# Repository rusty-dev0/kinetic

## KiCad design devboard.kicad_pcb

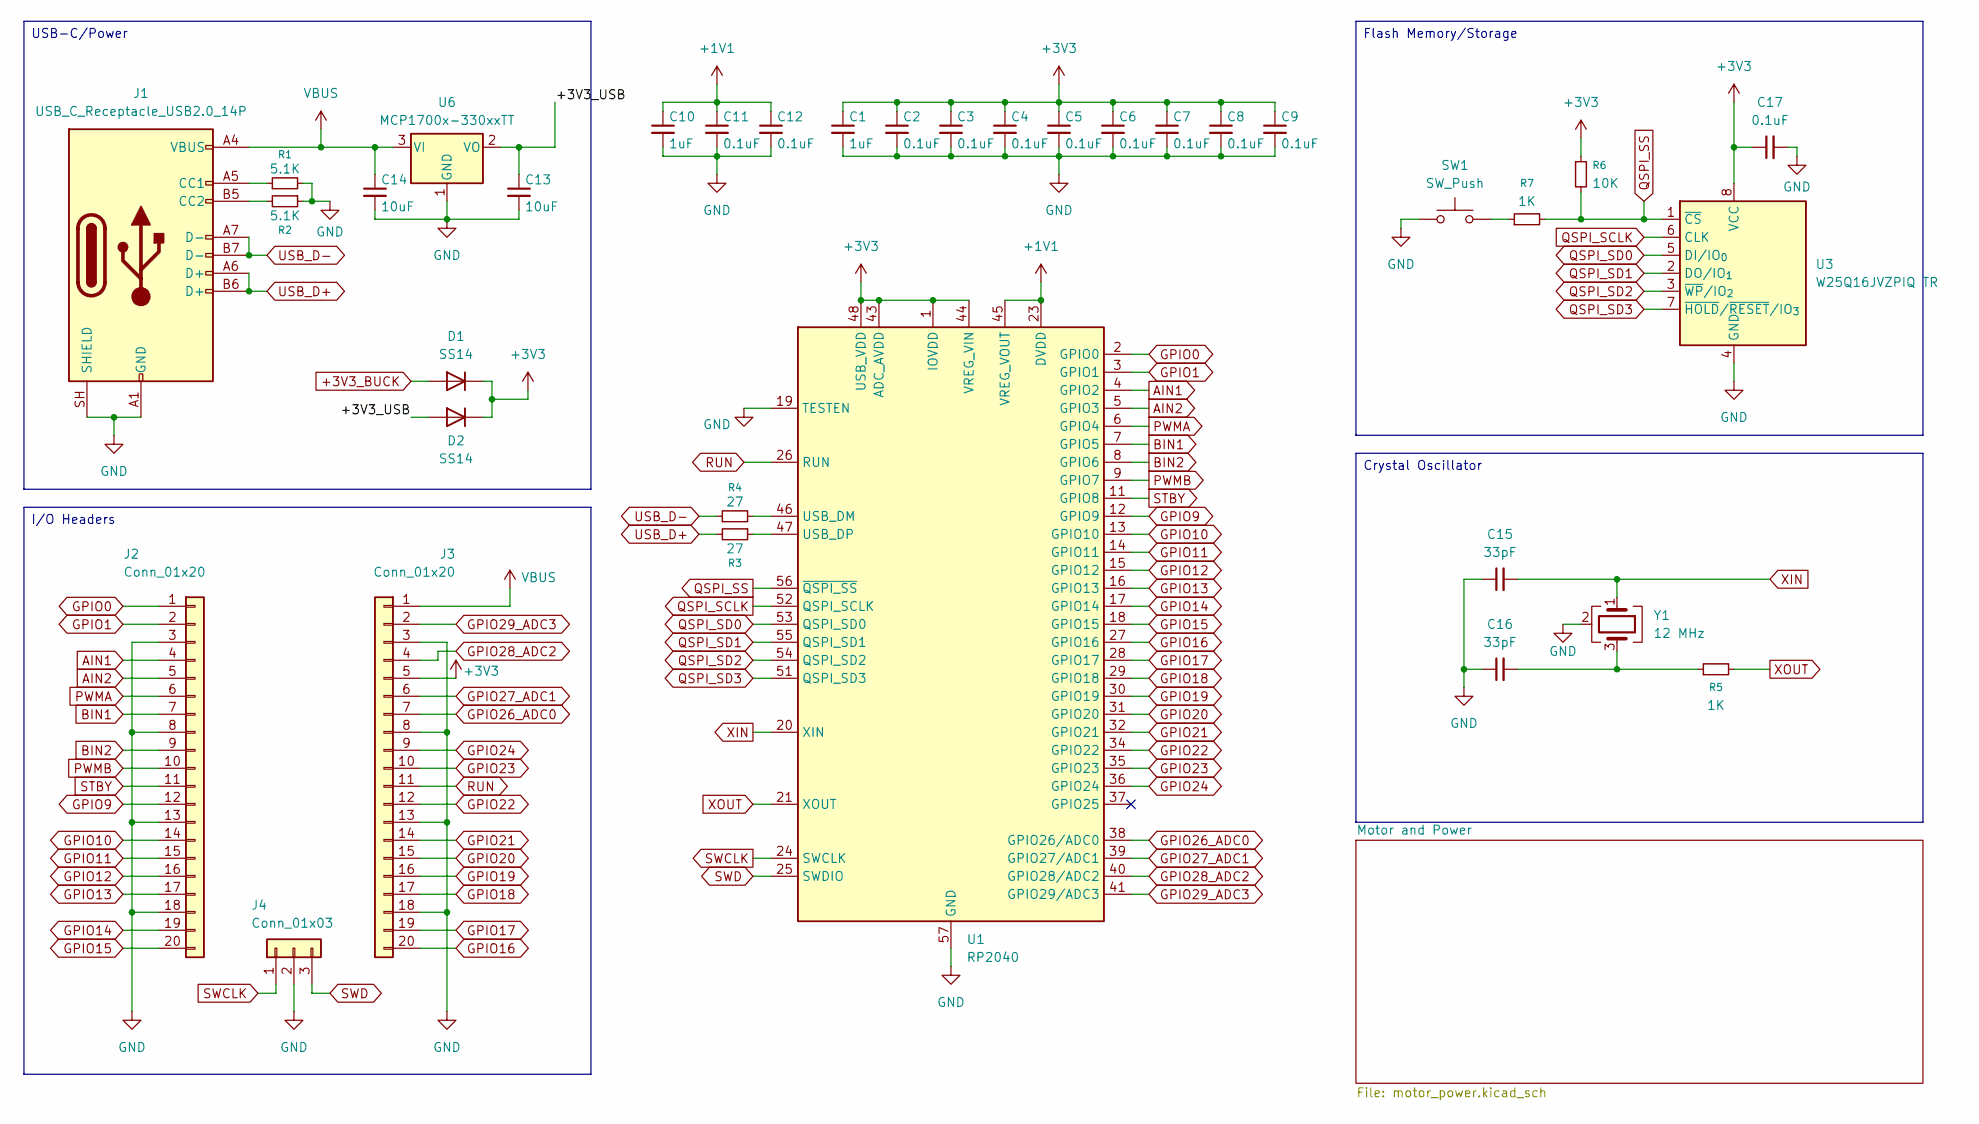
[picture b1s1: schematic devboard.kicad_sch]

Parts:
C1, C10: 1uF; C_0402_1005Metric
C2, C3, C4, C5, C6, C7, C8, C9, C11, C12, C17: 0.1uF; C_0402_1005Metric
C13, C14: 10uF; C_0603_1608Metric
C15, C16: 33pF; C_0402_1005Metric
D1, D2: SS14; D_SMA
J1: USB_C_Receptacle_USB2.0_14P; USB_C_Receptacle_HRO_TYPE-C-31-M-12
J2, J3: Conn_01x20; PinHeader_1x20_P2.54mm_Vertical
J4: Conn_01x03; FanPinHeader_1x03_P2.54mm_Vertical
R1, R2: 5.1K; R_0402_1005Metric
R3, R4: 27; R_0402_1005Metric
R5, R7: 1K; R_0402_1005Metric
R6: 10K; R_0402_1005Metric
SW1: SW_Push; SW_Push_SPST_NO_Alps_SKRK
U1: RP2040; QFN-56-1EP_7x7mm_P0.4mm_EP3.2x3.2mm
U3: W25Q16JVZPIQ TR; Winbond_USON-8-1EP_3x2mm_P0.5mm_EP0.2x1.6mm
U6: MCP1700x-330xxTT; SOT-23
Y1: 12 MHz; Crystal_SMD_3225-4Pin_3.2x2.5mm

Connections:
+1V1: C10.1, C11.1, C12.1, U1.23 (DVDD), U1.45 (VREG_VOUT), U1.50 (DVDD)
+3V3: C1.1, C2.1, C3.1, C4.1, C5.1, C6.1, C7.1, C8.1, C9.1, C17.1, D1.1 (K), D2.1 (K), J3.5, R6.1, U1.1 (IOVDD), U1.10 (IOVDD), U1.22 (IOVDD), U1.33 (IOVDD), U1.42 (IOVDD), U1.43 (ADC_AVDD), U1.44 (VREG_VIN), U1.48 (USB_VDD), U1.49 (IOVDD), U3.8 (VCC); also elsewhere on the board
+3V3_BUCK: D1.2 (A); also elsewhere on the board
/+3V3_USB: C13.1, D2.2 (A), U6.2 (VO); also elsewhere on the board
AIN1: J2.4, U1.4 (GPIO2); also elsewhere on the board
AIN2: J2.5, U1.5 (GPIO3); also elsewhere on the board
BIN1: J2.7, U1.7 (GPIO5); also elsewhere on the board
BIN2: J2.9, U1.8 (GPIO6); also elsewhere on the board
GND: C1.2, C2.2, C3.2, C4.2, C5.2, C6.2, C7.2, C8.2, C9.2, C10.2, C11.2, C12.2, C13.2, C14.2, C15.1, C16.1, C17.2, J1.A1 (GND), J1.A12 (GND), J1.B1 (GND), J1.B12 (GND), J1.SH (SHIELD), J2.3, J2.8, J2.13, J2.18, J3.3, J3.8, J3.13, J3.18, J4.2, R1.2, R2.1, SW1.1, U1.19 (TESTEN), U1.57 (GND), U3.4 (GND), U6.1 (GND), Y1.2 (G), Y1.4 (G); also elsewhere on the board
GPIO0: J2.1, U1.2 (GPIO0)
GPIO1: J2.2, U1.3 (GPIO1)
GPIO9: J2.12, U1.12 (GPIO9)
GPIO10: J2.14, U1.13 (GPIO10)
GPIO11: J2.15, U1.14 (GPIO11)
GPIO12: J2.16, U1.15 (GPIO12)
GPIO13: J2.17, U1.16 (GPIO13)
GPIO14: J2.19, U1.17 (GPIO14)
GPIO15: J2.20, U1.18 (GPIO15)
GPIO16: J3.20, U1.27 (GPIO16)
GPIO17: J3.19, U1.28 (GPIO17)
GPIO18: J3.17, U1.29 (GPIO18)
GPIO19: J3.16, U1.30 (GPIO19)
GPIO20: J3.15, U1.31 (GPIO20)
GPIO21: J3.14, U1.32 (GPIO21)
GPIO22: J3.12, U1.34 (GPIO22)
GPIO23: J3.10, U1.35 (GPIO23)
GPIO24: J3.9, U1.36 (GPIO24)
GPIO26_ADC0: J3.7, U1.38 (GPIO26/ADC0)
GPIO27_ADC1: J3.6, U1.39 (GPIO27/ADC1)
GPIO28_ADC2: J3.4, U1.40 (GPIO28/ADC2)
GPIO29_ADC3: J3.2, U1.41 (GPIO29/ADC3)
unnamed: C16.2, R5.1, Y1.3
unnamed: J1.A5 (CC1), R1.1
unnamed: J1.B5 (CC2), R2.2
unnamed: R7.1, SW1.2
unnamed: R4.2, U1.46 (USB_DM)
unnamed: R3.1, U1.47 (USB_DP)
PWMA: J2.6, U1.6 (GPIO4); also elsewhere on the board
PWMB: J2.10, U1.9 (GPIO7); also elsewhere on the board
QSPI_SCLK: U1.52 (QSPI_SCLK), U3.6 (CLK)
QSPI_SD0: U1.53 (QSPI_SD0), U3.5 (DI/IO_{0})
QSPI_SD1: U1.55 (QSPI_SD1), U3.2 (DO/IO_{1})
QSPI_SD2: U1.54 (QSPI_SD2), U3.3 (~WP/IO_{2})
QSPI_SD3: U1.51 (QSPI_SD3), U3.7 (~HOLD/~RESET/IO_{3})
QSPI_SS: R6.2, R7.2, U1.56 (~QSPI_SS), U3.1 (~CS)
RUN: J3.11, U1.26 (RUN)
STBY: J2.11, U1.11 (GPIO8); also elsewhere on the board
SWCLK: J4.1, U1.24 (SWCLK)
SWD: J4.3, U1.25 (SWDIO)
USB_D+: J1.A6 (D+), J1.B6 (D+), R3.2
USB_D-: J1.A7 (D-), J1.B7 (D-), R4.1
VBUS: C14.1, J1.A4 (VBUS), J1.A9 (VBUS), J1.B4 (VBUS), J1.B9 (VBUS), J3.1, U6.3 (VI); also elsewhere on the board
XIN: C15.2, U1.20 (XIN), Y1.1
XOUT: R5.2, U1.21 (XOUT)

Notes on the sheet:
Crystal Oscillator
USB-C/Power
Flash Memory/Storage
I/O Headers

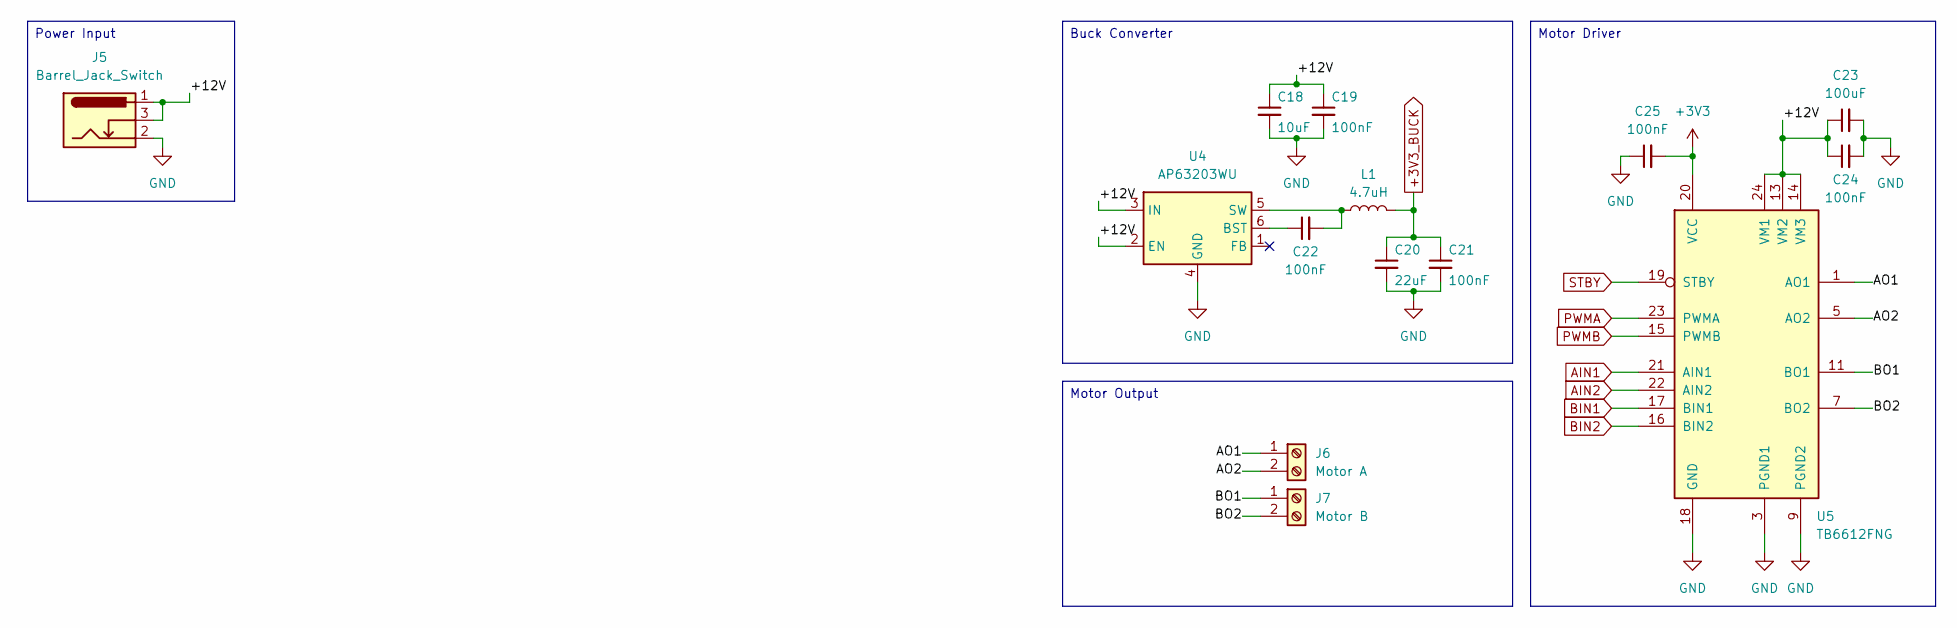
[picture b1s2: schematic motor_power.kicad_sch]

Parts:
C18: 10uF; C_0603_1608Metric
C19, C21, C22, C24, C25: 100nF; C_0402_1005Metric
C20: 22uF; C_0805_2012Metric
C23: 100uF; C_1206_3216Metric
J5: Barrel_Jack_Switch; BarrelJack_CUI_PJ-102AH_Horizontal
J6: Motor A; TerminalBlock_MaiXu_MX126-5.0-02P_1x02_P5.00mm
J7: Motor B; TerminalBlock_MaiXu_MX126-5.0-02P_1x02_P5.00mm
L1: 4.7uH; L_0805_2012Metric
U4: AP63203WU; TSOT-23-6
U5: TB6612FNG; SSOP-24_5.3x8.2mm_P0.65mm

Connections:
+3V3: C25.2, U5.20 (VCC); also elsewhere on the board
+3V3_BUCK: C20.1, C21.1, L1.2; also elsewhere on the board
/Motor and Power/+12V: C18.1, C19.1, C23.1, C24.1, J5.1, J5.3, U4.2 (EN), U4.3 (IN), U5.13 (VM2), U5.14 (VM3), U5.24 (VM1)
/Motor and Power/AO1: J6.1, U5.1 (AO1), U5.2 (AO1)
/Motor and Power/AO2: J6.2, U5.5 (AO2), U5.6 (AO2)
/Motor and Power/BO1: J7.1, U5.11 (BO1), U5.12 (BO1)
/Motor and Power/BO2: J7.2, U5.7 (BO2), U5.8 (BO2)
AIN1: U5.21 (AIN1); also elsewhere on the board
AIN2: U5.22 (AIN2); also elsewhere on the board
BIN1: U5.17 (BIN1); also elsewhere on the board
BIN2: U5.16 (BIN2); also elsewhere on the board
GND: C18.2, C19.2, C20.2, C21.2, C23.2, C24.2, C25.1, J5.2, U4.4 (GND), U5.3 (PGND1), U5.4 (PGND1), U5.9 (PGND2), U5.10 (PGND2), U5.18 (GND); also elsewhere on the board
unnamed: C22.1, U4.6 (BST)
unnamed: C22.2, L1.1, U4.5 (SW)
PWMA: U5.23 (PWMA); also elsewhere on the board
PWMB: U5.15 (PWMB); also elsewhere on the board
STBY: U5.19 (STBY); also elsewhere on the board

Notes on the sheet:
Motor Output
Power Input
Buck Converter
Motor Driver

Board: 2 copper layers, 50 parts (0 on the bottom side), 61 nets, no tracks yet.

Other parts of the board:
U2: NCP1117-3.3_SOT223; SOT-223-3_TabPin2

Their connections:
/+3V3_USB: U2.2 (VO); also elsewhere on the board
GND: U2.1 (GND); also elsewhere on the board
VBUS: U2.3 (VI); also elsewhere on the board

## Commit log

2026-04-19 finished initial schematic
2026-04-21 added barrel jack and buck converter
2026-04-22 connected motor driver
2026-04-22 began working on PCB
2026-05-02 finished first prototype
2026-05-07 added gerber files
